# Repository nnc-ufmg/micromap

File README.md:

MicroMAP: Low cost, high performance package for electrophysiological recording
===============================================================================
<div align="center">

<br/>
<br/>

 **About**

**MicroMAP** is a Python based electrophysiological aquisition system that combines the
portability of the raspberry pi and the versatility of the intan chip to harness the powerful 
combination of open source hardware and software to create a low cost, high performance package
for electrophysiological recording.

 **Getting started**

To get started, please see the installation page in the documentation. There you will find instructions on how to install MicroMAP on your raspberry pi and how to get started with the software.

 **Documentation**

_Online link coming soon_

<br/>

_**Note**_
 _This project is currently in its working beta phase._

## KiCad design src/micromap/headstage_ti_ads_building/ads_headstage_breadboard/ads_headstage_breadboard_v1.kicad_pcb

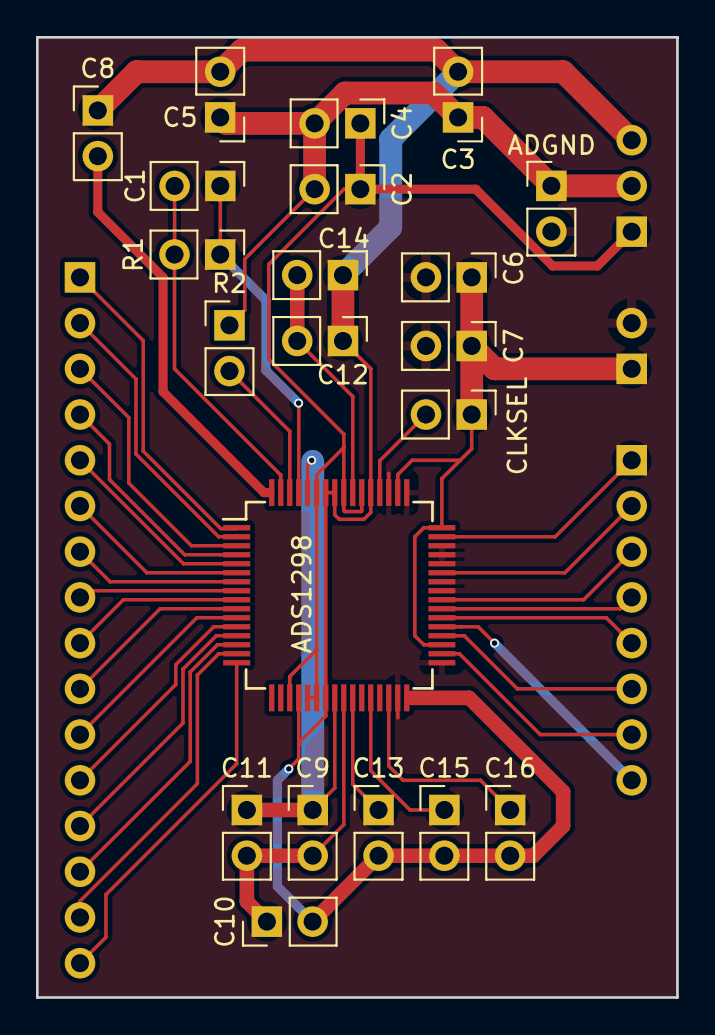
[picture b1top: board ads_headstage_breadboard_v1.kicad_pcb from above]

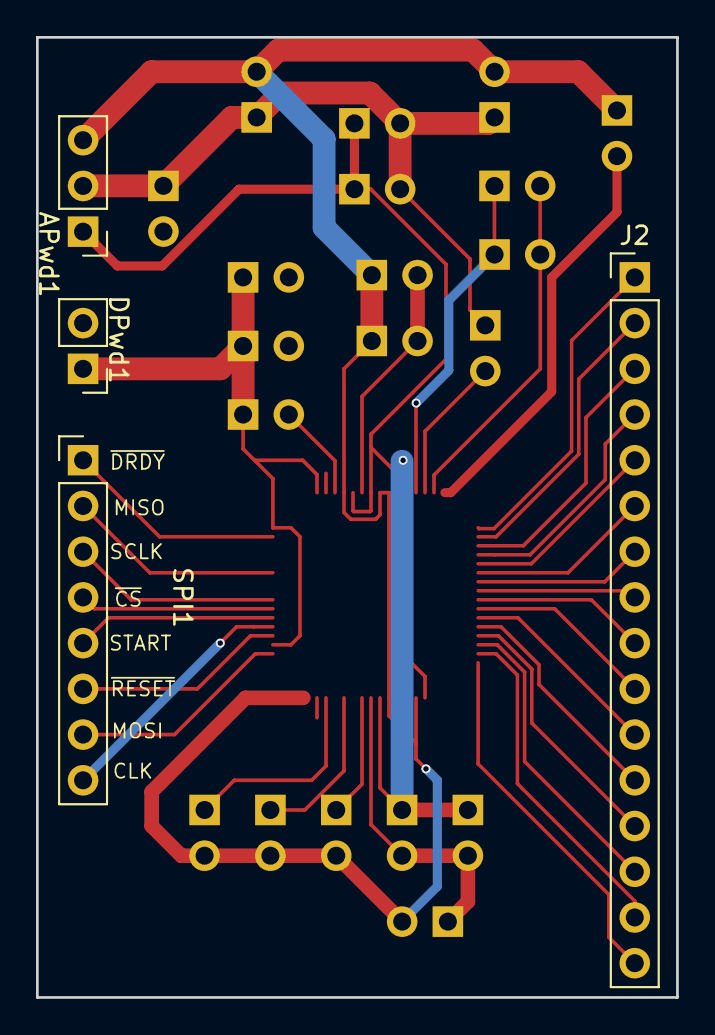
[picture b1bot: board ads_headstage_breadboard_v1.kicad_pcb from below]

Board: 2 copper layers, 35.6 x 53.3 mm, 25 parts (4 on the bottom side), 40 nets.

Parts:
ADGND: Jumper_NO_Small; PinHeader_1x02_P2.54mm_Vertical
ADS1298: ADS1298; TQFP-64_10x10mm_Pitch0.5mm
APwd1: Conn_01x03; PinHeader_1x03_P2.54mm_Vertical
C1: 1nf; PinHeader_1x02_P2.54mm_Vertical
C2, C3, C6, C10, C12, C13, C16: 1uF; PinHeader_1x02_P2.54mm_Vertical
C4, C5, C7, C9, C14: 0.1uF; PinHeader_1x02_P2.54mm_Vertical
C8: 100pf; PinHeader_1x02_P2.54mm_Vertical
C11: 10uF; PinHeader_1x02_P2.54mm_Vertical
C15: 22uF; PinHeader_1x02_P2.54mm_Vertical
CLKSEL: Jumper_NO_Small; PinHeader_1x02_P2.54mm_Vertical
DPwd1: Conn_01x02; PinHeader_1x02_P2.54mm_Vertical
J2: Conn_01x16_Female; PinHeader_1x16_P2.54mm_Vertical
R1, R2: 1M; PinHeader_1x02_P2.54mm_Vertical
SPI1: Conn_01x08; PinHeader_1x08_P2.54mm_Vertical

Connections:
/ADS1298/RLDIN: ADS1298.62, R2.2
/ADS1298/RLDINV: ADS1298.61, C1.1, R1.1
/ADS1298/RLDREF: ADS1298.24, ADS1298.60, C9.1, C11.1
/AGND: ADGND.1, APwd1.2, C2.2, C3.1, C4.2, C5.1, R2.1
/AVDD: ADS1298.19, ADS1298.21, ADS1298.22, ADS1298.54, ADS1298.56, ADS1298.59, APwd1.1, C2.1, C4.1
/AVSS: ADS1298.20, ADS1298.23, ADS1298.32, ADS1298.53, ADS1298.57, ADS1298.58, APwd1.3, C3.2, C5.2, C8.1, C10.2, C12.1, C13.2, C14.1, C15.2, C16.2
/CLK: ADS1298.37, SPI1.8
/CLKSEL: ADS1298.52, CLKSEL.2
/DGND: ADGND.2, ADS1298.31, ADS1298.33, ADS1298.41, ADS1298.42, ADS1298.44, ADS1298.45, ADS1298.46, ADS1298.49, ADS1298.51, C6.2, C7.2, DPwd1.2
/DVDD: ADS1298.35, ADS1298.48, ADS1298.50, C6.1, C7.1, CLKSEL.1, DPwd1.1
/IN1N: ADS1298.15, J2.15
/IN1P: ADS1298.16, J2.16
/IN2N: ADS1298.13, J2.13
/IN2P: ADS1298.14, J2.14
/IN3N: ADS1298.11, J2.11
/IN3P: ADS1298.12, J2.12
/IN4N: ADS1298.9, J2.9
/IN4P: ADS1298.10, J2.10
/IN5N: ADS1298.7, J2.7
/IN5P: ADS1298.8, J2.8
/IN6N: ADS1298.5, J2.5
/IN6P: ADS1298.6, J2.6
/IN7N: ADS1298.3, J2.3
/IN7P: ADS1298.4, J2.4
/IN8N: ADS1298.1, J2.1
/IN8P: ADS1298.2, J2.2
/MISO: ADS1298.43, SPI1.2
/MOSI: ADS1298.34, SPI1.7
/RDLout: ADS1298.63, C1.2, R1.2
/SPI_CLK: ADS1298.40, SPI1.3
/START: ADS1298.38, SPI1.5
/~CS: ADS1298.39, SPI1.4
/~DRDY: ADS1298.47, SPI1.1
/~RESET: ADS1298.36, SPI1.6
unnamed: ADS1298.25, C9.2, C10.1, C11.2
unnamed: ADS1298.26, C13.1
unnamed: ADS1298.28, C15.1
unnamed: ADS1298.30, C16.1
unnamed: ADS1298.55, C12.2, C14.2
unnamed: ADS1298.64, C8.2

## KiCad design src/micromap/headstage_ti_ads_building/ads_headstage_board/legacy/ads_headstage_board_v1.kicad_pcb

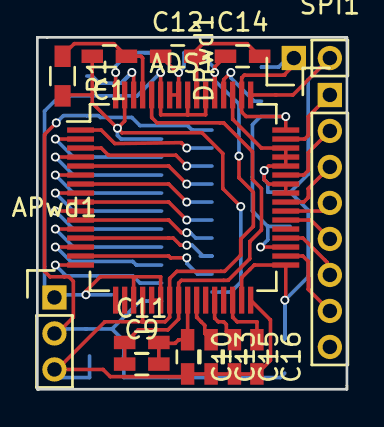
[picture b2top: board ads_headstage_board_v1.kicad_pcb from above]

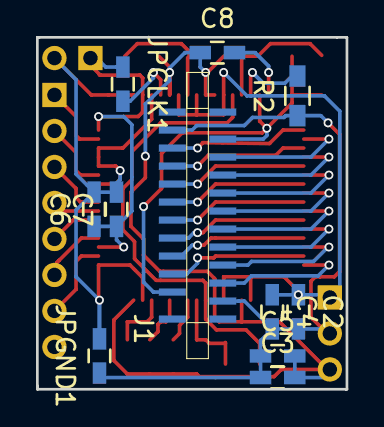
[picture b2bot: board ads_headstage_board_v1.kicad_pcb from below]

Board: 2 copper layers, 17.2 x 19.5 mm, 25 parts (11 on the bottom side), 39 nets.

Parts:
ADS1: ADS1298; TQFP-64_10x10mm_Pitch0.5mm
APwd1: Conn_01x03; Pin_Header_Straight_1x03_Pitch2.00mm
C1: 1nf; C_0603_HandSoldering
C2, C3, C6, C10, C12, C13, C16: 1uF; C_0603_HandSoldering
C4, C5, C7, C9, C14: 0.1uF; C_0603_HandSoldering
C8: 100pf; C_0603_HandSoldering
C11: 10uF; C_0603_HandSoldering
C15: 22uF; C_0603_HandSoldering
DPwd1: Conn_01x02; Pin_Header_Straight_1x02_Pitch2.00mm
J1: FFCfemale20
JPCLK1: Jumper_NO_Small; C_0603_HandSoldering
JPGND1: Jumper_NO_Small; C_0603_HandSoldering
R1, R2: 1M; R_0603_HandSoldering
SPI1: Conn_01x08; Pin_Header_Straight_1x08_Pitch2.00mm

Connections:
/ADS1298/RLDIN: ADS1.62, R2.2
/ADS1298/RLDINV: ADS1.61, C1.1, R1.1
/ADS1298/RLDREF: ADS1.24, ADS1.60, C9.1, C11.1
/AGND: APwd1.2, C2.2, C3.1, C4.2, C5.1, J1.1, J1.20, JPGND1.1, R2.1
/AVDD: ADS1.19, ADS1.21, ADS1.22, ADS1.54, ADS1.56, ADS1.59, APwd1.1, C2.1, C4.1
/AVSS: ADS1.20, ADS1.23, ADS1.32, ADS1.53, ADS1.57, ADS1.58, APwd1.3, C3.2, C5.2, C8.1, C10.2, C12.1, C13.2, C14.1, C15.2, C16.2
/CLKSEL: ADS1.52, JPCLK1.2
/DGND: ADS1.31, ADS1.33, ADS1.41, ADS1.42, ADS1.44, ADS1.45, ADS1.46, ADS1.49, ADS1.51, C6.2, C7.2, DPwd1.2, JPGND1.2
/DVDD: ADS1.35, ADS1.48, ADS1.50, C6.1, C7.1, DPwd1.1, JPCLK1.1
/IN1N: ADS1.15, J1.17
/IN1P: ADS1.16, J1.18
/IN2N: ADS1.13, J1.15
/IN2P: ADS1.14, J1.16
/IN3N: ADS1.11, J1.13
/IN3P: ADS1.12, J1.14
/IN4N: ADS1.9, J1.11
/IN4P: ADS1.10, J1.12
/IN5N: ADS1.7, J1.9
/IN5P: ADS1.8, J1.10
/IN6N: ADS1.5, J1.7
/IN6P: ADS1.6, J1.8
/IN7N: ADS1.3, J1.5
/IN7P: ADS1.4, J1.6
/IN8N: ADS1.1, J1.3
/IN8P: ADS1.2, J1.4
/MISO: ADS1.43, SPI1.2
/MOSI: ADS1.34, SPI1.7
/RDLout: ADS1.63, C1.2, J1.2, J1.19, R1.2
/SPI_CLK: ADS1.40, SPI1.3
/START: ADS1.38, SPI1.5
/~CS: ADS1.39, SPI1.4
/~DRDY: ADS1.47, SPI1.1
/~RESET: ADS1.36, SPI1.6
unnamed: ADS1.25, C9.2, C10.1, C11.2
unnamed: ADS1.26, C13.1
unnamed: ADS1.28, C15.1
unnamed: ADS1.30, C16.1
unnamed: ADS1.55, C12.2, C14.2
unnamed: ADS1.64, C8.2

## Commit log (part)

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2022-09-26 Version 0.0 files
    All the files that have been produced so far have been attached to the repository. This is the functional version 0.0 that we will start working on as a team
2022-09-26 Version 0.0 - Upload all files
    In this commit all files produced to build the system was uploaded. This is the version 0.0 and is the group work starting point.
2022-10-07 Add validation data
    A ECG test was permofed (07/10/22) to validate the interface. The records were made in OpenEphys and in NNC interface and are in te folder
2022-10-11 GUI with layout grids
    Initial part to fix the issue with missfitted labels
2022-10-11 Code development and file renaming
2022-10-11 Fix some bugs in the analysis
2022-10-12 Created layouts for the record tab
2022-10-12 Fix clipping buttons in the advanced tab
    - CONTINUE TO RECORD and CANCEL buttons
    that are on the bottom half of the tab were clipping
    through the bottom of the screen
2022-10-12 Finished base layouts on the advanced tab
    -- There is an excption:
    -The spaces to send messages and receive them are
    separated in two segments and this is causing a lot
    of trouble when grouping into a layout.
    -- Possible solutions:
    - Create a different design to accomodate the fixed
2022-10-12 Minor correction to ADC chip label
2022-10-14 Removal of unused buttons:
    - Remove unused zoom_in buttons
2022-10-14 Add reminder to check the timer function
    The timer function is not working properly. It is not showing the right
    cloked time. This is a reminder to check the timer function.
    - a TODO was added to the code in the interface_visual.py file
    - see line 824
2022-10-14 Add tutorial on commit template
    - Create a pdf presentation on how to use a
    commit template on vscode
2022-10-15 Added Vscode and Github presentation
    - Simple introduction to Github and VScode
    - Some commands and aspects of each tool
2022-10-15 Added first version with scrolling area working properly
    - Created the remaining layouts
    - Refined to accomodate nested layouts
    - Deleted the old interface_gui_layout.ui
    - Added the new interface_gui_v2.0.ui with the new layouts
    in the interface there was only one scroll area, now there are two:
    one for the settings and one for the plots. The settings area
2022-10-15 Created .gitignore file
    Ensure that unwanted files not tracked by Git remain untracked
2022-10-16 Added stylesheet to scroll area (advanced tab)
    - Now the scroll bars are the expected blue color
    The stylesheet, now that there were two scroll areas
    was missing from the settings area. This commit
    adds a stylesheet to that.
2022-10-21 Add stylesheet to the main window instead of specific widgets to avoid a bug in which the scrollbar was not stylized correctly.
    - Add stylesheet to MainWindow QWidget
    - Add stylesheet to the NNC_inBrain layout
    - Adjust buttons that were not aligned correctly in the advanced tab
2022-10-24 Create system_case_V2.skp
    Case v2.
    Update and Fixes:
    - removed ghost lines
    - improved expansion spaces
    - height increased
    - socket pins removed. Replaced by screws holes.
2022-10-25 System Case_update_02
    - R11 position adjusted
    - *stl and gcode and *x3g filed updated
2022-10-26 System case update
    Change:
    - incresed width by 4 mm.
    - *.x3g file from flash forge software
2022-10-31 Update all files and analysis
    - Added experiment data
    - Updated the analysis code
    - Updated old files
    - Renamed files and folders
2022-10-31 Update validation files and folders
    - Rename folders
    - Moved files
    - Organazid file stream
    - Update analysis code
2022-10-31 Update the data analysis - The OpenEphys data was recorded in 1000Hz (because I don't know) - Rename some files - Update de code to adapt to new folders
2022-11-02 Validation analysis almost finished
    - Update the code to identify files automatically
    - Resample mathed created
    - Offset removal applied
    - All signals seems to be equals in both systems!
2022-11-10 Create a docs folder and base to use sphinx
    - Create a docs folder
    - Create documentation files (rst)
    - Create build files (makefile, make.bat, conf.py)
    - Create a temporary logo image
2022-11-17 Create pip install
    - Organize the repo to be pip installable
    - Created __init__.py files to include the folders as modules
2022-11-18 Update documentation
    - Mounting tutorial
2022-11-24 Renamed the mounting.srt file to the correct extension mounting.rst
    - Added new section to index.rst
    - Fixed the figure indexing inside conf.py and index.rst that was
    causing the figures to not be displayed
    - Added a line separator inside the index.rst below the figure using
    the "|" character
    - Removed an "x" character in mounting.rst that were causing a warning
2022-12-01 Add comments to Sphinx
    Adding comments in formatting for Sphinx
2022-12-01 Add ToolTip
    Addition of Tooltips to application buttons and titles
2022-12-03 Create autodoc files
    - Created modules file to be a module index
    - Currently we only have 1 module (micromap)
    - Created the micromap.rst file to gather all functions and
    classes
    - Currently the subdivision is being done inside of
    micromap.interface.rst
2022-12-16 Add comments to code
    Some comments was added on the code
2022-12-17 Add comments to code
    Recommiting the comments to code
2022-12-19 Update the validation code
    - run all comparisions
2022-12-22 Update modules.rst and interface_visual.py
    - Modules.rst had insufficient underlining for the title and this
    was causing warnings when building the documentation.
    - interface_visual.py had a missing blank space after the head
    comment, crashing the documentation build.
2022-12-24 Move docs folder to root
2022-12-24 Create an overview rst file
    - This contains text that will be displayed separate
    from the index (when the user clicks on the logo)
2022-12-24 Change the format of the index.rst file
    - Removed the title
    - Add a subtitle centered
2022-12-24 Changed the conf.py file to add the correct path insertion
    - The folder structure now is changed, so the
    inclusion should reflect that (Being that the main
    package is inside of a src folder)
2022-12-24 Created a new folder and files
    - interface_functions.rst and interface_visual.rst. These will contain
    the documentation for the API
    - The image parts.png is the image that will be used to describe the
    parts of the API as demonstrated in the lading page
2022-12-24 Changed the comment style of the versioning
    - The previous style was spilling into the autodoc
    functionality of sphinx
    - Included a overview to the modules.rst
2022-12-24 Fix a simple mistake when creating a TOC tree
    - The overview TOC tree was creating duplicates of the
    content
    - Removing the caption and adding a centered text fixed
    this issue
2022-12-24 Fix broken logo link on README
2022-12-25 Add new requirements
    - Create a requirements.txt with updated
    requirements for installation
    - Update the install_requires field of the
    setup.cfg
2023-01-02 Aesthetic changes and interface file update
    - The old inerface.gui file was removed and the interface_v2.0
    was renamed to take its place
    - The interaface was changed to have the minified logo
    - The interface window now have the minified logo and
    the proper package name
2023-05-03 Update to run on RPi
    - Add setup.py
    - Update to run on Windows and Linux (/ and \\ problem)
2023-06-01 Update the validation_analyisis code - .py to .ipynb - clean the validation code and comment - clean the validation folder
2023-10-25 Commit to mantain the update
    - validation_analysis modifications
2023-11-01 ads1298
2023-11-07 Update the validation notebook to qualification
2024-07-23 Trying to ptimize the plot
2024-07-23 rollback to last working version - focus optimization on new branch
2024-08-05 feature mudança do eixo y -- editar start_view_mode
2024-08-08 plot changes
2024-08-09 Correction of the dislocated ADS1298 data buffer
    The "start recording" code was wrongly placed in the ADS1298 data buffer.
    This caused the data buffer to be filled with zeros, and shifted the data, causing the status word to be read incorrectly.
    - src/micromap/interface/interface_functions.py: Corrected the start recording code.
    - src/micromap/interface/interface_visual.py: Added a read() to remove characters from buffer.
    - started to implement the read_file_ads.m MATLAB routine to read the saved ADS1298 data.
2024-10-10 Major changes in threads
    - Change the plot threads
    - Threadpool stead threads
    - Is not the final version
2024-10-22 Correcting the plot and testing the new plotter
2024-10-24 Plot fixed and progress bar fixed
    - Thread to progress bar
    - Fixed thread to plot
    - This version is FUNCTIONAL
2024-11-04 Last threads update
    - The threads are working and simple
    - Thread to update the statistics
    - Data saving is working
2025-03-21 Update validation
    - Code to sync the records using stumpy
2025-04-17 Update new way to read bytes from arduino
2025-04-20 Publishing updates
    - New threads to read and save
    - New way to save data
    - Plot optimization
    - Read functions and new class to read MicroMAP data
2025-04-21 Plot optimization
    - Thread to plot
    - Plot now is updated by time (second to second)
2025-04-21 Desabale opengl
2025-04-21 Raspberry Pi adjust
2025-04-21 Update RPi
2025-04-21 RPi last try
2025-04-21 More RPi updates
2025-04-21 Vaaaaai RPi
2025-04-21 Last updates???
2025-04-24 Saving update
2025-04-24 Logging to debug
2025-04-24 Increasing the time to emit signals
2025-04-24 add change attr advanced
2025-04-24 Update package loss
2025-04-24 Fix timoutbug
2025-04-24 Update the path and add command to save the data remaining in the buffer after complete record
2025-04-29 Uses the header to count the samples in microseconds
    - Before: header with packet counter (16bits)
    - After: header with microsec( _) counter (32bits)
2025-04-29 Update analysis codes
    - Function to read the data and analyze the packets
    - Function to read the EKG data
    - Class to read MicroMAP data
2025-04-29 Repo cleaning
    - Deleted old folders and codes
    - Renamed one analysis file
    - Moved one analysis file to correct folder
2025-04-29 Add the PCB files
    - ADS headstage design
    - ADS breadboard design
    - Rename some files
    - Delete old/unused files
2025-04-30 Add ADS reader class
2025-04-30 Update on validation ads codes
2025-04-30 Microcontroller ADS folder
2025-04-30 Updates on ads functions and square
    - Clean data
